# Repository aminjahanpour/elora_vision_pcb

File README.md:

# Elora Vision PCB

KiCad files for image_over_lora project PCB

## Goal
The most important goal for image_over_lora project is to keep the costs low.
So I've made it such that you could simply use already existing boards to set up and work with the porject [just as explained here](https://github.com/aminjahanpour/image_over_lora_android).
For doing that you'd need two boards: a black pill and an a LoRa module.

It could be that a PCB that integerates both of those two modules <b> would cost less</b>.

That is why I've started this project.

## Specs
### General
This is a compact 4-layer PBC powered only via its USB 2.0 connection (Type C plug).
In total, 6 LEDs are included to provide a decent elaboration on both USB and Radio data 
tx/rx processes and possible errors.
A 2-pin SW debug plug is provided for debugging and uploading the firmware.
Also, a USART plug is provided.
To lower the final cost, I used JLCPCB basic parts (rather than extended parts) where I could.
The LCSC part numbers for the parts are included in the BOM.
Use these part numbers to look up the exact components on the JLCPCB website.

### MCU
The board is centered around an STM32F411CEU6 chip.
It provides enough processing power for our Elora Vision firmware.

### LoRa
I chose RX1276 as for the LoRa module because this is perhaps the most common one in North America where I live.
The design targets 915 MHz abiding to the legal frequency bands in Canada.
I went with the IPEX antenna connection because it allows for more flexibility in antenna placement on the UAV.
The radio circuitry is based on the below sources:
- [Semtech reference design](https://www.semtech.com/products/wireless-rf/lora-connect/sx1276)
- [a design by Modtronix](https://modtronix.com/product/inair9b/)

[Also check out my question on StackExchange](https://electronics.stackexchange.com/questions/670470/circuitry-around-sma-for-a-lora-module-pcb-rx1276) regarding the radio circuitry. The given answer is pretty informative.

### Credits

- [A great guide for implementing USB-C in your KiCad projects](https://github.com/jenschr/USB-C-Connectors)
- I highly recommend taking [Phil's Lab PCB design courses](https://www.phils-lab.net/). It helped me a lot.

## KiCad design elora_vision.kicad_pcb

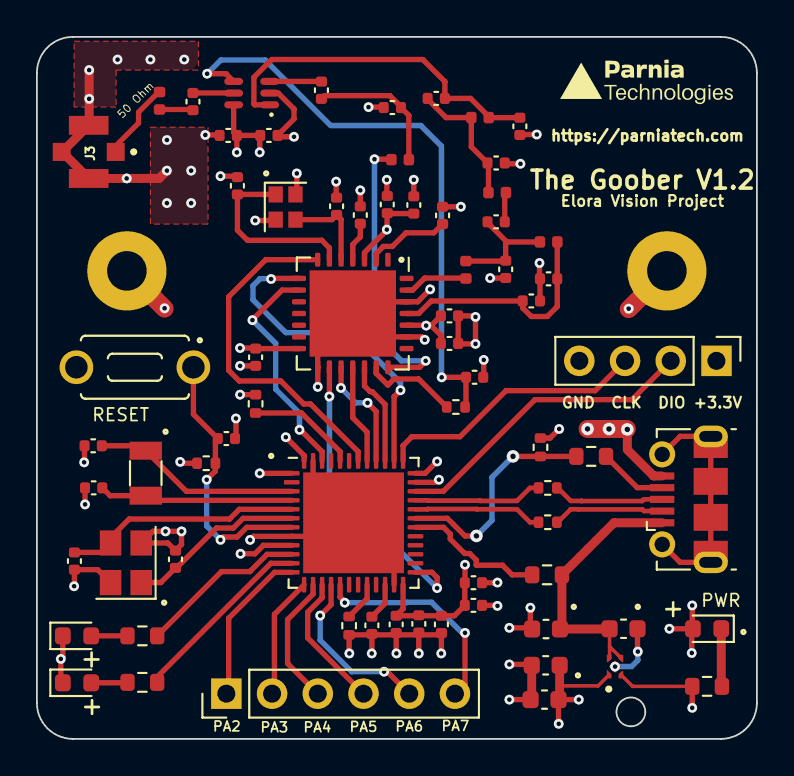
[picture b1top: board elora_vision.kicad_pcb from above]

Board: 4 copper layers, 40.0 x 39.0 mm, 72 parts (0 on the bottom side), 57 nets.

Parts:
B2: SW_SPST_SKHLAAA010; SKHLAAA010
C1, C3, C8, C9, C10, C18, C20, C21, C22, C36: 100nF; C_0402_1005Metric
C2: 10uF; C_0402_1005Metric
C4, C23: 1nF; C_0402_1005Metric
C6: 2.2uF; C_0402_1005Metric
C7: 4.7uF; C_0402_1005Metric
C11, C12: 1uF; C_0603_1608Metric
C14, C15: 100nF; C_0603_1608Metric
C16, C25, C26, C32, C37: 47pF; C_0402_1005Metric
C19, C38, C40, C43: 10pF; C_0402_1005Metric
C24, C30: 3.3pF; C_0402_1005Metric
C29, C34: 8.2pF; C_0402_1005Metric
C31: 1.5pF; C_0402_1005Metric
C33: 10nF; C_0402_1005Metric
C35: 22pF; C_0402_1005Metric
C39, C41: 2.2pF; C_0402_1005Metric
D1: LED_GREEN_PWR; LED_0603_1608Metric
D2: LED_GREEN_1; LED_0603_1608Metric
D3: LED_YELLOW_1; LED_0603_1608Metric
H3, H4: MountingHole_Pad; MountingHole_2.2mm_M2_Pad
J1: USB_B_Micro; USB_Micro-B_Molex-105017-0001
J2: Conn_01x04_Male; PinHeader_1x04_P2.54mm_Vertical
J3: IPEX_73412-0114; MOLEX_73412-0114
J4: Conn_01x06_Male; PinHeader_1x06_P2.54mm_Vertical
L1: 0R; L_0402_1005Metric
L2: 10nH Wire; L_0402_1005Metric
L4: 4.7nH Wire; L_0402_1005Metric
L5: 5.6nH Wire; L_0402_1005Metric
L6: 33nH; L_0402_1005Metric
L7: 2.2nH Wire; L_0402_1005Metric
Q1: 32MHz; Crystal_SMD_2016-4Pin_2.0x1.6mm
R1, R8, R9, R10, R13: 560; R_0603_1608Metric
R2, R3, R6: 10K; R_0402_1005Metric
R4, R5: 22; R_0402_1005Metric
R7: 1k; R_0402_1005Metric
R15: 100k; R_0402_1005Metric
U1: STM32F411CEU6; QFN-48-1EP_7x7mm_P0.5mm_EP5.6x5.6mm
U2: AP7340-12FS4-7; VREG_AP7340D-25FS4-7
U5: PE4259; SOT65P215X110-6N
U6: SX1276; QFN-28-1EP_6x6mm_P0.65mm_EP4.8x4.8mm
Y4: 12 MHz (C9002); Crystal_SMD_3225-4Pin_3.2x2.5mm
Y5: 32.768 kHz; Crystal_SMD_3215-2Pin_3.2x1.5mm

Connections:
+3.3V: C2.1, C3.2, C4.1, C7.2, C8.2, C9.2, C10.1, C12.2, C15.1, C16.2, C18.2, C22.1, C36.1, C37.1, D1.2 (A), J2.1, R3.2, R15.1, U1.1 (VBAT), U1.9 (VDDA), U1.24 (VDD), U1.36 (VDD), U1.48 (VDD), U2.1 (VOUT), U5.6 (VDD), U6.3 (VBAT_ANA), U6.14 (VBAT_DIG), U6.24 (VBAT_RF)
+5V: C11.2, C14.1, J1.1 (VBUS), R13.2, U2.3 (EN), U2.4 (VIN)
/MCU/D+: J1.3 (D+), R5.2
/MCU/D-: J1.2 (D-), R4.2
BOOT0: R2.1, U1.44 (BOOT0)
GND: B2.2, C1.1, C2.2, C3.1, C4.2, C6.1, C7.1, C8.1, C9.1, C10.2, C12.1, C14.2, C15.2, C16.1, C18.1, C19.2, C20.1, C21.1, C22.2, C23.2, C24.2, C29.2, C30.2, C32.2, C33.2, C34.2, C36.2, C37.2, C38.2, C39.2, C40.2, C41.2, C43.2, D2.1 (K), D3.1 (K), H3.1, H4.1, J1.5 (GND), J2.4, J3.2, J3.3, J3.4, Q1.2, Q1.4, R2.2, R6.1, R8.2, U1.8 (VSSA), U1.23 (VSS), U1.35 (VSS), U1.47 (VSS), U1.49 (VSS), U2.2 (GND), U5.2 (GND), U6.15 (GND), U6.23 (GND), U6.26 (GND), U6.29 (GND), Y4.2, Y4.4
HSE_IN: C40.1, U1.5 (PH0), Y4.3
HSE_OUT: C38.1, U1.6 (PH1), Y4.1
LED_GREEN: R9.2, U1.10 (PA0)
LED_YELLOW_1: R10.2, U1.11 (PA1)
LORA_DIO0: U1.38 (PA15), U6.8 (DIO0)
LORA_DIO1: U1.46 (PB9), U6.9 (DIO1)
LORA_MISO: U1.40 (PB4), U6.17 (MISO)
LORA_MOSI: U1.41 (PB5), U6.18 (MOSI)
LORA_NSS: U1.39 (PB3), U6.19 (NSS)
LORA_RESET: U1.42 (PB6), U6.7 (NRESET)
LORA_SCK: U1.25 (PB12), U6.16 (SCK)
LSE_IN: C39.1, U1.3 (PC14), Y5.1
LSE_OUT: C41.1, U1.4 (PC15), Y5.2
NRST: B2.1, C1.2, R3.1, U1.7 (NRST)
unnamed: C24.1, C25.1, L2.2
unnamed: C26.1, L1.1
unnamed: C29.1, C31.1, L4.1, L5.2
unnamed: C34.1, C35.1, L6.2, L7.2
unnamed: C35.2, L5.1
unnamed: D1.1 (K), R8.1
unnamed: D2.2 (A), R9.1
unnamed: D3.2 (A), R10.1
unnamed: J1.4 (ID), R1.2
unnamed: J3.1, L1.2
unnamed: C6.2, U1.22 (VCAP1)
unnamed: C11.1, U2.5 (EXP)
unnamed: C23.1, R7.2, U5.4 (CTRL)
unnamed: C30.1, C31.2, L4.2, U5.1 (RF1)
unnamed: C25.2, U5.3 (RF2)
unnamed: C26.2, U5.5 (RFC)
unnamed: L7.1, U6.27 (PA_BOOST)
unnamed: L2.1, U6.21 (RFI_HF)
unnamed: R7.1, U6.20 (RXTX/RFMOD)
unnamed: C20.2, U6.2 (VR_ANA)
unnamed: C21.2, U6.4 (VR_DIG)
unnamed: C32.1, C33.1, L6.1, U6.25 (VR_PA)
unnamed: C43.1, Q1.3, U6.5 (XTA)
unnamed: C19.1, Q1.1, U6.6 (XTB)
PA2: J4.1, U1.12 (PA2)
PA3: J4.2, U1.13 (PA3)
PA4: J4.3, U1.14 (PA4)
PA5: J4.4, U1.15 (PA5)
PA6: J4.5, U1.16 (PA6)
PA7: J4.6, U1.17 (PA7)
PA9_VBUS: R13.1, U1.30 (PA9)
PA10: R1.1, R15.2, U1.31 (PA10)
PA13: J2.2, U1.34 (PA13)
PA14: J2.3, U1.37 (PA14)
PB2: R6.2, U1.20 (PB2)
USB_D+: R5.1, U1.33 (PA12)
USB_D-: R4.1, U1.32 (PA11)

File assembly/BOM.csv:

Comment,Designator,Footprint,LCSC
"SW_SPST_SKHLAAA010","B2","SKHLAAA010:SKHLAAA010",""
"1uF","C11,C12","Capacitor_SMD:C_0603_1608Metric",""
"100nF","C14,C15","Capacitor_SMD:C_0603_1608Metric",""
"47pF","C16,C25,C26,C32,C37","Capacitor_SMD:C_0402_1005Metric",""
"100nF","C1,C3,C8,C9,C10,C18,C20,C21,C22,C36","Capacitor_SMD:C_0402_1005Metric",""
"10pF","C19,C38,C40,C43","Capacitor_SMD:C_0402_1005Metric",""
"10uF","C2","Capacitor_SMD:C_0402_1005Metric",""
"3.3pF","C24,C30","Capacitor_SMD:C_0402_1005Metric",""
"8.2pF","C29,C34","Capacitor_SMD:C_0402_1005Metric",""
"1.5pF","C31","Capacitor_SMD:C_0402_1005Metric",""
"10nF","C33","Capacitor_SMD:C_0402_1005Metric",""
"22pF","C35","Capacitor_SMD:C_0402_1005Metric",""
"2.2pF","C39,C41","Capacitor_SMD:C_0402_1005Metric",""
"1nF","C4,C23","Capacitor_SMD:C_0402_1005Metric",""
"2.2uF","C6","Capacitor_SMD:C_0402_1005Metric",""
"4.7uF","C7","Capacitor_SMD:C_0402_1005Metric",""
"LED_GREEN_PWR","D1","LED_SMD:LED_0603_1608Metric",""
"LED_GREEN_1","D2","LED_SMD:LED_0603_1608Metric",""
"LED_YELLOW_1","D3","LED_SMD:LED_0603_1608Metric",""
"MountingHole_Pad","H3,H4","MountingHole:MountingHole_2.2mm_M2_Pad",""
"USB_B_Micro","J1","Connector_USB:USB_Micro-B_Molex-105017-0001",""
"Conn_01x04_Male","J2","Connector_PinHeader_2.54mm:PinHeader_1x04_P2.54mm_Vertical",""
"IPEX_73412-0114","J3","MOLEX_73412-0114",""
"Conn_01x06_Male","J4","Connector_PinHeader_2.54mm:PinHeader_1x06_P2.54mm_Vertical",""
"0R","L1","Inductor_SMD:L_0402_1005Metric",""
"10nH Wire","L2","Inductor_SMD:L_0402_1005Metric",""
"4.7nH Wire","L4","Inductor_SMD:L_0402_1005Metric",""
"5.6nH Wire","L5","Inductor_SMD:L_0402_1005Metric",""
"33nH","L6","Inductor_SMD:L_0402_1005Metric",""
"2.2nH Wire","L7","Inductor_SMD:L_0402_1005Metric",""
"32MHz","Q1","Crystal:Crystal_SMD_2016-4Pin_2.0x1.6mm",""
"560","R1,R8,R9,R10,R13","Resistor_SMD:R_0603_1608Metric",""
"100k","R15","Resistor_SMD:R_0402_1005Metric",""
"10K","R2,R3,R6","Resistor_SMD:R_0402_1005Metric",""
"22","R4,R5","Resistor_SMD:R_0402_1005Metric",""
"1k","R7","Resistor_SMD:R_0402_1005Metric",""
"STM32F411CEU6","U1","Package_DFN_QFN:QFN-48-1EP_7x7mm_P0.5mm_EP5.6x5.6mm",""
"AP7340-12FS4-7","U2","AP7340D:VREG_AP7340D-25FS4-7",""
"PE4259","U5","PE4259:SOT65P215X110-6N",""
"SX1276","U6","Package_DFN_QFN:QFN-28-1EP_6x6mm_P0.65mm_EP4.8x4.8mm",""
"12 MHz (C9002)","Y4","Crystal:Crystal_SMD_3225-4Pin_3.2x2.5mm",""
"32.768 kHz","Y5","Crystal:Crystal_SMD_3215-2Pin_3.2x1.5mm",""
